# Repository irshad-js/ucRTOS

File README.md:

# ucRTOS
A real time operating system for microcontroller projects with Windows and Linux software emulation.

The goal of this project is a simple ecosystem for fast and easy development of microcontroller projects. The platform is based on the FreeRTOS real-time kernel.

The ecosystem consists of:
* Display (320x240 LCD)
* File system (SD-Card)
* Input device (NES-Gamepad)
* Bus Interface (RS485)
* RF Interface (NRF24)
* Real time kernel (FreeRTOS v9.0.0)
* Simple menu system

For faster development there are simulators which run under Windows and Linux. This allows quick protoyping on e.g. menus or images without the need of flashing the microcontroller after each change. The simulators do not have real time behaviour. This is because of either Windows nor Linux are real time operating systems. However, the deterministic task switching behaviour of the real time scheduler is simulated correctly. Simulators are tested on Windows 7 with Visual Studio 2017 and Arch Linux.

Supported embedded devices so far:
* STM32F4Discovery (STM32F407VG)

Supported simulators so far:
* Windows 7 with Visual Studio 2017
* Linux with GCC

## Building Instructions

### STM32F4

#### Compile the binary
```
make
```

#### Flash the microcontroller

To flash the .bin file you need to install **st-link** first.
After that you can just flash by typing:

```
make flash
```

### Windows Simulator with Visual Studio 2017

Note: The simulator does not work properly on Windows 10. It can be compiled and run but the timings are incorrect. Therefore **it is suggested using Windows 7**.

The LCD simulation is based on the wxWidgets GUI Library which is included as a sub repository. Before you are able to build the simulator you need to clone and build wxWidgets first:

#### Cloning wxWidgets subrepository
```
1. run cmd.exe
2. cd \<Path to ucRTOS repository\>
3. git submodule init
4. git submodule update
```

This meight take a few minutes to complete.

#### Build wxWidgets

1. Browse to platform\simulators\lib\wxWidgets\build\msw and open wx_vc15.sln. 
2. Migrate the Project for Visual Studio 2017 by selecting **Solution 'wx_vc15'** in Solution explorer and then select **Project > Retarget Solution**, check all vcxproj files, select the latest Windows SDK Version and click **ok**.
3. Select Win32 as target platform and hit Build Solution from Build menu.
4. After compiling is finished, the simulator can be built.

### Linux Simulator

#### Build the simulator

#### Cloning wxWidgets subrepository
```
1. cd \<Path to ucRTOS repository\>
2. git submodule init
3. git submodule update
```

1. Run the simulator by executing **platform/simulators/linux/bin/run_ucrtos.sh**
On first execution wxWidgets will be build which can take a few minutes. If code of ucrtos is changed it will be rebuild automatically.

### Debugging using Eclipse

Create a Debug configuration and select **platform/simulators/linux/bin/ucrtos.elf** als target. Since the purpose of the simulators is debugging, the executable is always built with debug information.

### Pointers to remember

The simulator project file for Visual Studio misses a source file and header file related to magiclantern. Locate them and create links for them for successful build.

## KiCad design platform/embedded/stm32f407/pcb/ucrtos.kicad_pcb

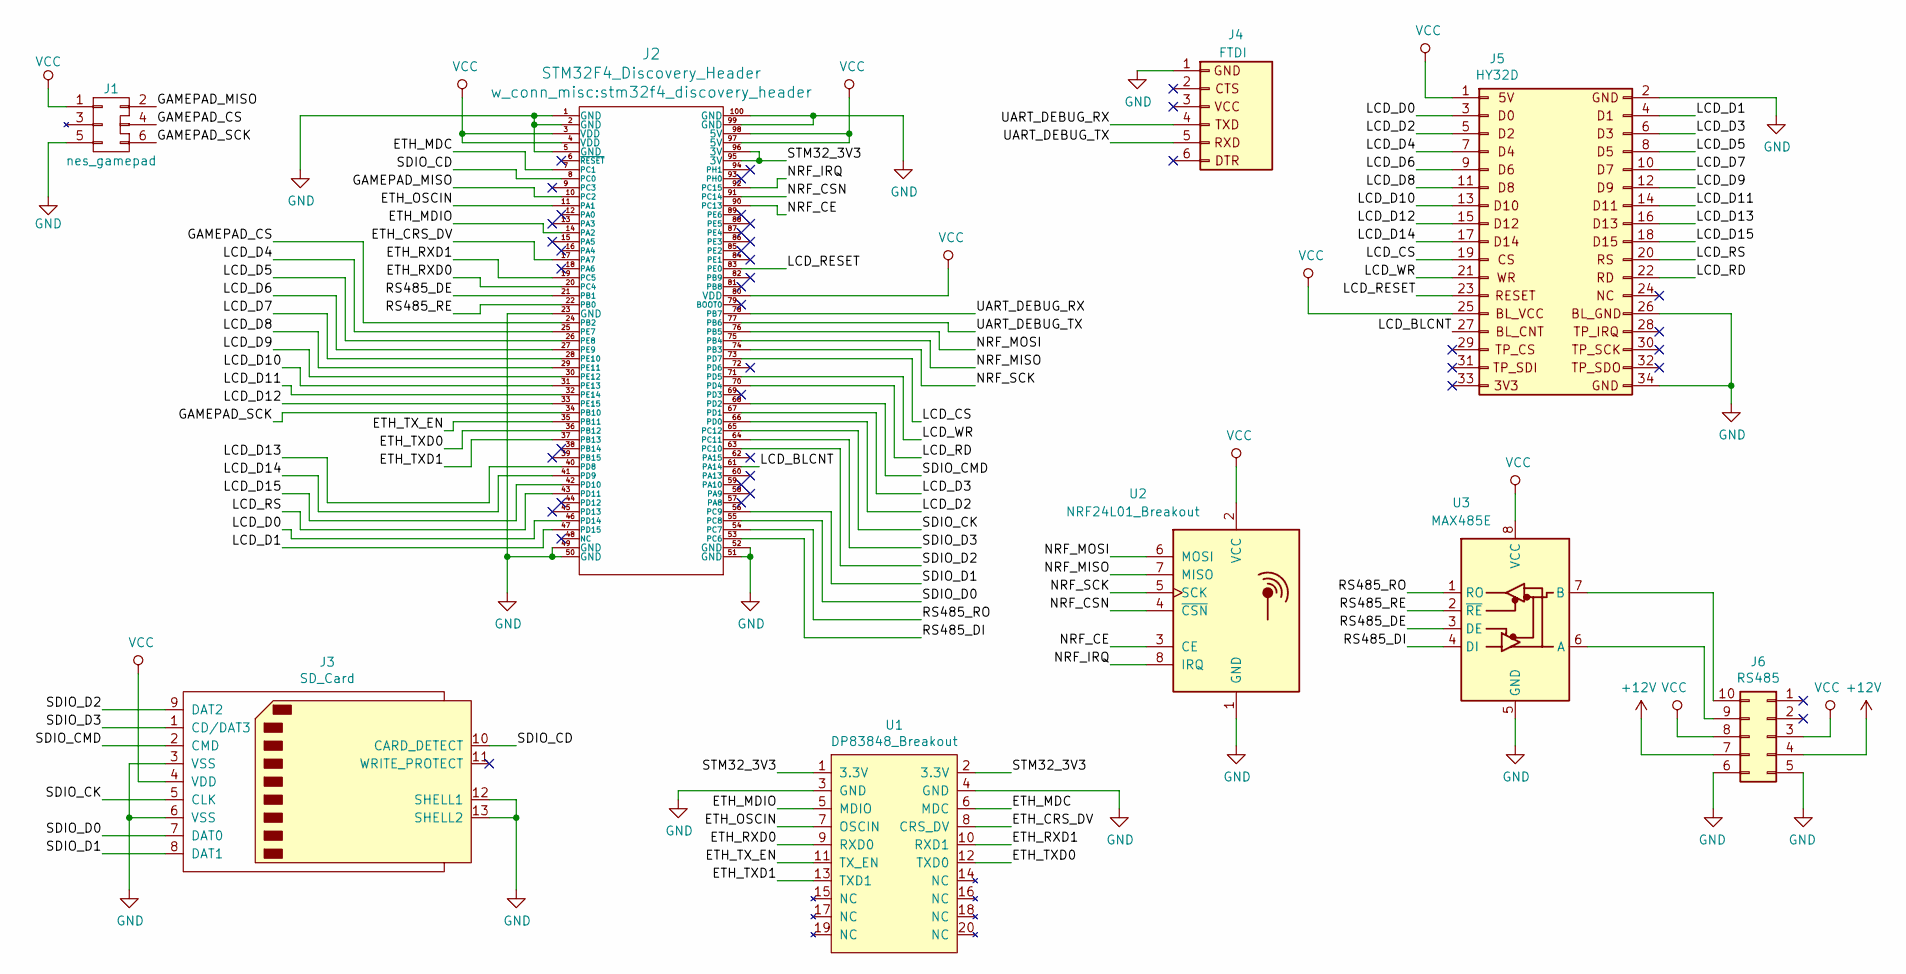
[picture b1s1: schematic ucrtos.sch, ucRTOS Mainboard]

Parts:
J1: nes_gamepad; IDC-Header_2x03_P2.54mm_Vertical
J2: STM32F4_Discovery_Header; stm32f4_discovery_header
J3: SD_Card; IDC-Header_2x08_P2.54mm_Vertical
J4: FTDI; PinHeader_1x06_P2.54mm_Vertical
J5: HY32D; IDC-Header_2x17_P2.54mm_Vertical
J6: RS485; IDC-Header_2x05_P2.54mm_Vertical
U1: DP83848_Breakout; PinSocket_2x10_P2.54mm_Horizontal
U2: NRF24L01_Breakout; PinHeader_2x04_P2.54mm_Vertical
U3: MAX485E; DIP-8_W7.62mm

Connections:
+12V: J6.4, J6.7
/ETH_CRS_DV: J2.17 (PA7), U1.8 (CRS_DV)
/ETH_MDC: J2.7 (PC1), U1.6 (MDC)
/ETH_MDIO: J2.14 (PA2), U1.5 (MDIO)
/ETH_OSCIN: J2.11 (PA1), U1.7 (OSCIN)
/ETH_RXD0: J2.20 (PC4), U1.9 (RXD0)
/ETH_RXD1: J2.19 (PC5), U1.10 (RXD1)
/ETH_TXD0: J2.36 (PB12), U1.12 (TXD0)
/ETH_TXD1: J2.37 (PB13), U1.13 (TXD1)
/ETH_TX_EN: J2.35 (PB11), U1.11 (TX_EN)
/GAMEPAD_CS: J1.4 (LATCH), J2.24 (PB2)
/GAMEPAD_MISO: J1.2 (MISO), J2.10 (PC2)
/GAMEPAD_SCK: J1.6 (SCK), J2.34 (PB10)
/LCD_BLCNT: J2.61 (PA14), J5.27 (D13)
/LCD_CS: J2.73 (PD7), J5.19 (TP_SO)
/LCD_D0: J2.46 (PD14), J5.3 (D2)
/LCD_D1: J2.47 (PD15), J5.4 (D4)
/LCD_D2: J2.66 (PD0), J5.5 (D6)
/LCD_D3: J2.67 (PD1), J5.6 (D8)
/LCD_D4: J2.25 (PE7), J5.7 (D10)
/LCD_D5: J2.26 (PE8), J5.8 (D12)
/LCD_D6: J2.27 (PE9), J5.9 (D14)
/LCD_D7: J2.28 (PE10), J5.10 (CS)
/LCD_D8: J2.29 (PE11), J5.11 (WR)
/LCD_D9: J2.30 (PE12), J5.12 (RESET)
/LCD_D10: J2.31 (PE13), J5.13 (BL_VDD)
/LCD_D11: J2.32 (PE14), J5.14 (BL_CNT)
/LCD_D12: J2.33 (PE15), J5.15 (TP_CS)
/LCD_D13: J2.40 (PD8), J5.16 (TP_SI)
/LCD_D14: J2.41 (PD9), J5.17 (3V3)
/LCD_D15: J2.42 (PD10), J5.18 (GND)
/LCD_RD: J2.70 (PD4), J5.22 (BLGND)
/LCD_RESET: J2.83 (PE0), J5.23 (NC)
/LCD_RS: J2.43 (PD11), J5.20 (TP_SCK)
/LCD_WR: J2.71 (PD5), J5.21 (TP_IRQ)
/NRF_CE: J2.90 (PC13), U2.3 (CE)
/NRF_CSN: J2.91 (PC14), U2.4 (~CSN)
/NRF_IRQ: J2.92 (PC15), U2.8 (IRQ)
/NRF_MISO: J2.75 (PB4), U2.7 (MISO)
/NRF_MOSI: J2.76 (PB5), U2.6 (MOSI)
/NRF_SCK: J2.74 (PB3), U2.5 (SCK)
/RS485_DE: J2.21 (PB1), U3.3 (DE)
/RS485_DI: J2.53 (PC6), U3.4 (DI)
/RS485_RE: J2.22 (PB0), U3.2 (~RE)
/RS485_RO: J2.54 (PC7), U3.1 (RO)
/SDIO_CD: J2.8 (PC0), J3.10 (CARD_DETECT)
/SDIO_CK: J2.65 (PC12), J3.5 (CLK)
/SDIO_CMD: J2.68 (PD2), J3.2 (CMD)
/SDIO_D0: J2.55 (PC8), J3.7 (DAT0)
/SDIO_D1: J2.56 (PC9), J3.8 (DAT1)
/SDIO_D2: J2.63 (PC10), J3.9 (DAT2)
/SDIO_D3: J2.64 (PC11), J3.1 (CD/DAT3)
/STM32_3V3: J2.95 (3V), J2.96 (3V), U1.1 (3.3V), U1.2 (3.3V)
/UART_DEBUG_RX: J2.78 (PB7), J4.4
/UART_DEBUG_TX: J2.77 (PB6), J4.5
GND: J1.5 (GND), J2.1 (GND), J2.2 (GND), J2.5 (GND), J2.23 (GND), J2.49 (GND), J2.50 (GND), J2.51 (GND), J2.52 (GND), J2.99 (GND), J2.100 (GND), J3.3 (VSS), J3.6 (VSS), J3.12 (SHELL1), J3.13 (SHELL2), J4.1, J5.2 (D0), J5.26 (D15), J5.34 (GND), J6.5, J6.6, U1.3 (GND), U1.4 (GND), U2.1 (GND), U3.5 (GND)
unnamed: J6.9, U3.6 (A)
unnamed: J6.10, U3.7 (B)
VCC: J1.1 (VCC), J2.3 (VDD), J2.4 (VDD), J2.80 (VDD), J2.97 (5V), J2.98 (5V), J3.4 (VDD), J5.1 (5V), J5.25 (RS), J6.3, J6.8, U2.2 (VCC), U3.8 (VCC)

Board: 2 copper layers, 9 parts (0 on the bottom side), 59 nets, no tracks yet.

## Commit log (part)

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2017-06-25 init
2017-07-04 clean up
2017-07-04 add ARM_CM4F port
2017-07-15 remove FreeRTOS-Plus directory
2017-07-15 rename MSVC project from WIN32 to ucRTOS
2017-07-15 move msdev project to platform/windows directory
2017-07-15 platform: windows: fix filters
2017-07-15 move main.c to core directory
2017-07-15 rename main.c to core_main.c
2017-07-15 move FreeRTOS from root to lib directory
2017-07-15 add platform stm32f407
2017-07-15 core_main.c: remove conio.h include
2017-07-15 move windows port specific code to platform main
2017-07-15 add basic hardware abstraction layer with led blink sample
2017-07-15 update Makefile
2017-07-15 platform: stm32f407: add hardware.c
2017-07-15 platform: stm32f407: remove native led toggle code from main.c
2017-07-15 platform: stm32f407: remove utils.h
2017-07-15 platform: stm32f407: build fix
2017-07-15 platform: stm32f407: remove unused functions
2017-07-16 platform: stm32f407: improve directory structure
2017-07-16 platform: stm32f407: add coocox ide project
2017-07-16 Makefile: build fix
2017-07-16 rename stm32_flash.ld to link.ld
2017-07-16 platform: stm32f407: coocox: use same linker script as make file
2017-07-29 platform stm32f4: add function matrix
2017-07-29 platform stm32f4: update connection matrix
2017-07-30 platform stm32f4: remove DAC / USART2 from init function
2017-08-01 platform stm32f4: add delay timer and error state
2017-08-01 platform stm32f4: add tm_stm32f4_usb_vcp library (but not used yet)
2017-08-05 add debug interface using UART1
2017-08-05 all exception handlers lead to errorState()
2017-08-05 FreeRTOSConfig.h: improve indention
2017-08-06 add basic SD card support
2017-08-08 add NES game pad driver
2017-09-10 correct placement of mystdio lib
2017-09-16 add platform linux
2017-09-17 core main: remove old sample code
2017-10-01 platform windows: use relative include path for mystdio lib
2017-10-01 add wxWidgets submodule
2017-10-01 platform windows: fix paths
2017-10-02 platform windows: does now compile with wx
2017-10-07 README.md: add build instructions
2017-10-07 README.md: fix typos and formatting issues
2017-10-09 implement LCD drawing routine (bad performance)
2017-10-14 platform windows: migrate to visual studio 2017
2017-10-15 implement display HAL
2017-10-15 display.h: fix declaration order
2017-10-16 add AsciiLib
2017-10-16 basic implementation of FSM and slot based menu
2017-10-16 States: MainMenu: add some functionality
2017-10-16 platform windows: implement crappy input device handling
2017-10-18 LCD: use 16 bit frame buffer
2017-10-22 platform stm32f4: build fix
2017-10-22 README.md: add build instructions for stm32f4
2017-11-05 move frame buffer to core
2017-11-05 remove obsolete frame buffer
2017-11-05 decrease color depth of framebuffer to 8 bit (2:3:2)
2017-11-05 do not hard code display resolution
2017-11-05 display: avoid setting pixels out of bounds
2017-11-05 platform stm32f4: fix display driver
2017-11-05 platform stm32f4: experimentally added coocox ide linker script
2017-11-05 add ssd1289 driver
2017-11-05 platform stm32f4: implement strcpy_s
2017-11-05 platform stm32f4: coocox ide build fix
2017-11-05 platform stm32f4: remove coocox linker script again
2017-11-09 use heap_5 + make menu work on stm32f4
2017-11-11 add about screen
2017-11-11 add about state
2017-11-11 fix tick of old state after transitting back
2017-11-11 platform stm32f4: avoid integer overflow on hal_clock()
2017-11-11 rename hal_clock() -> uptimeMs()
2017-11-11 delayMs() + delayUs() are now hardware independent
2017-11-11 platform stm32f4: remove delay and clock timers
2017-11-12 proper initialization of input device
2017-11-12 add build date to about state
2017-12-18 states/about.c: show passed ticks
2017-12-18 display: clean up
2017-12-18 ucrtos.h: add FreeRTOS includes
2017-12-18 states/about.c: display clock ticks correctly
2017-12-18 core_main.c: increase integer overflow of upTimeMs() from ~1:00h to ~50 days
2017-12-19 add example state
2017-12-19 example screen: update comments / add newline
2017-12-19 platform windows: update project files
2017-12-19 adjust screen file names
2017-12-21 avoid some warnings
2017-12-21 avoid more warnings
2018-01-01 platform stm32f407: build fix
2018-01-03 add basic schematic
2018-01-06 update pin mappings
2018-02-18 display: prepare 16 color frame buffer
2018-02-18 platform stm32f4: update pin mappings
2018-02-18 platform stm32f4: update Makefile
2018-02-18 aboutscreen: removed things
2018-02-18 display: add apple macintosh 16 color default palette array
2018-02-18 display 16 bit drawing works
2018-02-18 add image test screen
2018-02-18 platform win32: update msdev project files
2018-02-18 remove obsolete code #2
2018-02-18 imagetestscreen: draw nes gamepad
2018-02-18 reduce memory consumption of frame buffer
2018-02-18 display: use additional LUT for rendering
2018-02-18 core_main: disable debug task
2018-02-18 platform windows: beautify
2018-02-18 display: fix lut
2018-02-18 display: beautify
2018-02-19 display: lay out LUT to lut.h / lut.c
2018-02-20 lib: add eMIDI submodule
2018-02-21 add playermenucreen
2018-02-21 update eMIDI subrepo
2018-02-22 add playerscreen
2018-02-22 StackBasedFsm: avoid crash when onLeaveState is not set
2018-03-11 platform windows: midi player hal implementation
2018-03-11 implement simple MIDI player screen
2018-04-12 update eMIDI submodule
2018-04-14 build fix (but still linker error)
2018-04-14 Makefile: generate .map file
2018-04-14 Makefile: rename output.map -> ucrtos.map
2018-04-26 screens: use hal functions / add line breaks to printf
2018-04-26 platform stm32f4: implement hal_printf
2018-05-11 .gitmodules
2018-05-11 move NRF lib to lib subdir
2018-05-11 update skateboard screen
2018-05-11 it compiles somehow...
2018-05-11 update NRF24 submodule
2018-05-12 update NRF24 lib
2018-05-12 send NRF data on gamepad button press
2018-05-26 disable skateboard screen (platform windows build fix)
2018-05-26 exclude skateboardscreen + use eMIDI windows HAL
2018-05-27 Add sub menu for Floppy Orgel
2018-05-27 add 'Live Mode' screen
2018-05-27 add LockFreeFifo lib
2018-05-27 make live mode work
2018-05-27 LockFreeFifo: beautify
2018-11-25 platform linux simulator: add FreeRTOS Posix Simulator code
2018-11-25 linux simulator: remove Release config
2018-11-25 remove platform linux
2018-12-01 add button test screen
2018-12-01 beautify
2018-12-01 remove ParTest
2018-12-01 platform linux: modify eclipse project stuff...
2018-12-01 platform linux: remove AsyncIO
2018-12-01 Revert "minimalize main.c"
    This reverts commit c6281d740f0b3dd3e640782be4ecf173abbad804.
2018-12-01 Revert "platform linux: remove AsyncIO"
    This reverts commit 4908d7c23fc4dc2898342c874897267110734d7b.
2018-12-21 platform linux: rename linux -> linux_old
2018-12-21 platform linux: update FreeRTOS port to v9.0.0
2018-12-21 platform linux: add FreeRTOSConfig.h for v9.0.0
2018-12-21 platform linux: add Makefile
2018-12-21 platform linux: rename main.cpp -> main.c
2018-12-21 platform linux: compile FreeRTOS sources
2018-12-21 platform linux: add ucRTOS framework partially
2018-12-22 platform linux: add more parts of ucRTOS (eMIDI hal missing)
2018-12-22 platform linux: fix eMIDI hal
2018-12-22 platform linux: hal: implement eMidi_halTimeUs() + hal_printf
2018-12-22 platform linux: rework main.c to main.cpp
2018-12-22 platform linux: add wx frame / start call coreMain from thread
2018-12-22 platform linux: implement hacky wx initialization
2018-12-23 platform windows: add buttontestscreen.c
2018-12-23 platform linux: build fix
2018-12-23 platform linux: improve rendering mechanism
2018-12-23 core: InputDevice: beautify
2018-12-23 buttontestscreen: throttle drawing rate
2018-12-23 Makefile: beautify
2018-12-23 buttontestscreen: fix and improve debug output
2018-12-23 platform linux: implement MIDI device
2018-12-23 mainmenuscreen: add TODO
2018-12-23 remove linux_old
2018-12-24 platorm linux: build fix
2018-12-26 playerscreen: beautify
2019-01-04 Input device: processButton: remove duplicate argument
2019-01-04 Input device: call direction callback on direction button release
2019-01-04 platform linux: add nrf24 dummy implementation
2019-01-04 modify skateboardscreen so it also works in simulators
2019-01-04 mainmenuscreen: enable skateboardscreen again
2019-01-17 stm32f4_function_mappings.xml: colorize NRF24 + Ethernet pins
2019-01-17 platform stm32f4: add tm_delay lib
2019-01-17 platform stm32f4: add tm_gpio lib
2019-01-17 platform stm32f4: add defines.h for tm libs
2019-01-17 platform stm32f4: add attributes.h for tm libs
2019-01-17 platform stm32f4: change debug uart baudrate 9600 -> 115200
2019-01-17 update NRF24L01P submodule
2019-01-17 platform stm32f4: ssd1289: flip display contents
2019-01-17 stm32f4: pcb: migrate kicad project
2019-01-17 stm32f4 pcb: add w_connectors.lib
2019-01-17 stm32f4 pcb: add w_conn_misc stm32f4discovery footprint
2019-01-17 assign footprints / generate netlist
2019-01-19 stm32f4_function_mappings.xlsx: update NRF24 function mapping
2019-01-20 platform stm32f4: Makefile: fix typo
2019-01-26 platform stm32f4: pcb: add FTDI symbol + wire FTDI + LCD
2019-01-26 platform stm32f4: pcb: did some wiring...
2019-01-26 platform stm32f4: pcb: update pin mappings excel sheet
2019-01-28 platform stm32f4: pcb: wire NRF24
2019-01-28 stm32f4_function_mappings.xlsx: add NRF comments
2019-02-01 platform stm32f4: pcb: add dp83848.lib
2019-02-01 platform stm32f4: pcb: update ftdi.lib
2019-02-01 platform stm32f4: pcb: update hy32d.lib
2019-02-01 platform stm32f4: pcb: update pcb
2019-02-03 platform stm32f4: pcb: place parts on pcb
2019-02-04 fix mounting of sd card
2019-02-04 ffconf.h: fix LFN
2019-02-04 add SD Card Screen
2019-02-06 platform windows: build fix
2019-02-11 InputDevice: add check for onDirection callback before execute
2019-02-11 implement FloppyOrgel player
2019-02-14 platform linux: implement filesystem HAL
2019-02-14 skateboardscreen: brake -> decelerate
2019-02-15 platform linux: implement colored printf
2019-02-15 core_main: do not printf in blink task
2019-02-16 floppyorgelscreen: add newlines to printfs
2019-02-16 playermenuscreen: init file system
2019-02-16 implement livemodescreen
2019-02-16 platform linux: implement RS485 handling
2019-05-02 platform linux: avoid helper buffers on colored print
2019-05-02 platform linux: hardware.c: build fix, further avoid of helper buffers
2020-10-26 _examplescreen.c: add missing line breaks on printf calls
2020-10-31 add include dir of wx library
2020-11-06 platform linux: Makefile: add magiclanternscreen.c
2020-11-06 platform linux: add run_ucrtos.sh script
2020-11-06 README.md: update instructions for linux simulator
2020-11-08 platform linux: run_ucrtos.sh: only run after successful build
2020-11-08 SlotBasedMenu: remove SETTINGS_MENU + BROWSE_MENU type
2020-11-08 SlotBasedMenu: remove MenuType_t
2020-11-08 SlotBasedMenu.h: remove obsolete MENU_FILES_PER_PAGE define
2020-11-08 SlotBasedMenu.h: remove obsolete BrowseNewPageCallback definition
2020-11-08 SlotBasedMenu.h: remove obsolete settings menu callbacks
2020-11-08 SlotBasedMenu.h: build fix
2020-11-08 SlotBasedMenu.h: replace userMenuInit() by menuInit()
2020-11-08 screens: build fix
2020-11-29 platform windows: hardware.c: const correctness + improve some namings
2020-12-04 SlotBasedMenu: fix namings
2020-12-04 SlotBasedMenu: rename menuAddSlot() -> menuAddTransitSlot()
2020-12-04 SlotBasedMenu.c: draw HexValueSlot cursor + enable HexValueSlot navigation
2020-12-04 magiclanternscreen: use HexValueSlot for Address
2020-12-04 SlotBasedMenu.c: HexValueSlot: only highlight digit in edit mode
2020-12-04 SlotBasedMenu: HexValueSlot: implement enter and leave of edit mode
2020-12-04 magiclanternscreen: redraw screen on enter and leave of HexValueSlot edit mode
2020-12-04 magiclanternscreen: ignore button release on action and back + only redraw on HexValueSlot events
2020-12-04 _examplescreen: improve debug output
2020-12-05 magiclanternscreen: pass east + west cursor direction events to menu
2020-12-05 SlotBasedMenu: SlotBasedMenu: HexValueSlot: draw address digits
2020-12-05 SlotBasedMenu: HexValueMenu: make digits settable
